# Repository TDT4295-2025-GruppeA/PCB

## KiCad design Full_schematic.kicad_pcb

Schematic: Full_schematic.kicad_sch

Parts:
C1: 1210, 2.2µF/100V; C_1210_3225Metric
C2, C3, C60, C62, C63, C64: 22u; C_0805_2012Metric
C4, C7, C8, C9, C11, C14, C16, C19, C20, C21, C22, C23, C24, C25, C28, C29, C30, C31, C32, C39, C44, C59, C61, C65, C66, C67, C68, C69, C70: 470n; C_0805_2012Metric
C5, C13, C15, C17, C50, C54, C57, C78, C83, C84, C85, C86, C87, C88, C90, C95, C96: 100n; C_0805_2012Metric
C6: 100u; C_0805_2012Metric
C10, C12, C56, C91, C99: 10u; C_0805_2012Metric
C26: 3.3n; C_0805_2012Metric
C33, C36, C37, C71, C72: 47u; C_0805_2012Metric
C34: 330u; CP_EIA-3216-10_Kemet-I
C35: 100u; CP_EIA-2012-15_AVX-P
C38, C40, C41, C42, C43, C45, C46, C47, C51, C52, C53, C55, C58, C73, C74, C75, C76, C77: 4.7u; C_0805_2012Metric
C48, C49, C89, C94: 1u; C_0805_2012Metric
C80, C82: 6pF; C_0805_2012Metric
C92, C93: 2.2u; C_0805_2012Metric
C97: 0.1uF; C_0805_2012Metric
C101, C102, C103: 1u; CP_EIA-2012-15_AVX-P
D1: IR26-21C_L110_TR8; LED_1206_3216Metric
IC1: XC7A100T-1FTG256C; FTG256_AMD; Manufacturer_Part_Number XC7A100T-1FTG256C
J1: FFC3B11-40-T; FH12A40S05SH55; PARTREV A; DigiKey_Part_Number 2073-FFC3B11-40-TCT-ND
J2: CONN14_877591414_MOL
J3: Conn_ST_STDC14; PinHeader_2x07_P1.27mm_Vertical_SMD
J4: AMPHENOL_10067847-001RLF
J5: USB_B_Micro; CONN_10118192-0002LF_AMP
JP1, JP2, JP3, JP4: G800W306018EU; AMPHENOL_G800W306018EU; PARTREV B
L1: 18uH; L_0805_2012Metric
L2, L3: 1.5u; L_0805_2012Metric
L4, L6: 2.2u; L_0805_2012Metric
R1: 30.1k; R_0805_2012Metric
R2, R4, R10: 22.1k; R_0805_2012Metric
R3: 6.81k; R_0805_2012Metric
R5: 200; R_0805_2012Metric
R6, R25, R26, R30, R33, R34: 100; R_0805_2012Metric
R7, R8: 100k; R_0805_2012Metric
R9: 73.2k; R_0805_2012Metric
R12, R13: 4.7k; R_0805_2012Metric
R14, R16, R18, R20, R21, R24, R29, R32, R35, R37, R39, R41: 536; R_0805_2012Metric
R15, R17, R19, R22, R27, R31, R36, R38, R40: 270; R_0805_2012Metric
R23, R28, R55: 10k; R_0805_2012Metric
R42: THB001P; XDCR_COM-09032
R45, R85, R86: 1k; R_0805_2012Metric
R46, R47, R48, R49, R50, R51, R52, R53, R54, R56, R57, R58, R59, R60, R61, R62, R63, R64, R65, R66, R67, R68, R69, R70, R71, R72, R73, R74: 220; R_0805_2012Metric
R75, R76, R77, R78: 47; R_0805_2012Metric
R79, R80, R81, R82, R83, R84: 10K; R_0805_2012Metric
U1: 2S7A_0518S1U; SIP4_2S7A_GAP
U2, U6: IS66WVE4M16EBLL-70BLI; SOP80P1184X119-44N; Manufacturer_Part_Number CY62157EV30LL-55ZSXE
U3: TPS54294PWP; PWP16_2P31X2P46
U4: TPS54325PWPR; PWP14_2P31X2P46
U5, U8: SN74ALVC245PWR; PW20
U7: S25FL127S; SOIC127P800X216-8N
U9, U11, U14, U16: MAN72A
U10, U12, U15, U17: MC14511BDG; SOIC-16_ONS
U13: STM32U545VETxQ; LQFP-100_14x14mm_P0.5mm
U18, U19: PTS645SM43SMTR92LFS; SWITCH_43SMTR92LFS
Y1: 100Hz; CB3LV3C100M000000
Y2: 48MHz; Crystal_SMD_2520-4Pin_2.5x2.0mm

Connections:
+1V0: C7.1, C9.1, C14.1, C19.1, C21.1, C23.1, C28.1, C31.1, C34.1, C35.1, C39.1, C40.1, C43.1, C44.1, C47.1, C52.1, C55.1, C58.1, C60.1, C63.1, IC1.E10 (VCCBRAM_1), IC1.F7 (VCCINT_1), IC1.F9 (VCCINT_2), IC1.F11 (VCCBRAM_2), IC1.G6 (VCCINT_3), IC1.H9 (VCCINT_4), IC1.J6 (VCCINT_5), IC1.K9 (VCCINT_6), IC1.L8 (VCCINT_7), JP3.1, JP3.2, L3.2, R3.1, U4.1 (VO)
+1V8: C2.1, C3.2, C24.1, C29.1, C32.1, C36.1, C41.1, C45.1, IC1.G8 (VCCADC_0), IC1.G10 (VCCAUX_1), IC1.J10 (VCCAUX_2), IC1.K11 (VCCAUX_3), IC1.L10 (VCCAUX_4), JP1.1, JP1.2, L2.1, R1.1
A2: IC1.A2 (IO_L8N_T1_AD14N_35), U2.44 (A5)
B1: IC1.B1 (IO_L9N_T1_DQS_AD7N_35), U2.43 (A6)
B2: IC1.B2 (IO_L8P_T1_AD14P_35), U2.42 (A7)
B4: IC1.B4 (IO_L4P_T0_35), U2.41 (~OE)
B5: IC1.B5 (IO_L2N_T0_AD12N_35), U2.40 (~BHE)
BLUE: R14.2, R15.2; also elsewhere on the board
BLUE0: IC1.T9 (IO_L22P_T3_A05_D21_14), U5.6 (A5)
BLUE1: IC1.T8 (IO_L21N_T3_DQS_A06_D22_14), U5.7 (A6)
BLUE2: IC1.T7 (IO_L21P_T3_DQS_14), U5.8 (A7)
BLUE3: IC1.T5 (IO_L23N_T3_A02_D18_14), U5.9 (A8)
C1: IC1.C1 (IO_L9P_T1_DQS_AD7P_35), U2.37 (I/O14)
C2: IC1.C2 (IO_L7N_T1_AD6N_35), U2.36 (I/O13)
C3: IC1.C3 (IO_L7P_T1_AD6P_35); also elsewhere on the board
C4: IC1.C4 (IO_L12N_T1_MRCC_35); also elsewhere on the board
C6: IC1.C6 (IO_L5N_T0_AD13N_35); also elsewhere on the board
C7: IC1.C7 (IO_L5P_T0_AD13P_35); also elsewhere on the board
D1: IC1.D1 (IO_L10N_T1_AD15N_35), U2.35 (I/O12)
D3: IC1.D3 (IO_L11N_T1_SRCC_35), U2.32 (I/O11)
D4: IC1.D4 (IO_L12P_T1_MRCC_35), U2.31 (I/O10)
D5: IC1.D5 (IO_L6N_T0_VREF_35); also elsewhere on the board
D6: IC1.D6 (IO_L6P_T0_35), U2.30 (I/O9)
D8: IC1.D8 (IO_L6P_T0_15); also elsewhere on the board
D16: IC1.D16 (IO_L17N_T2_A25_15), U13.1 (PE2)
E1: IC1.E1 (IO_L15N_T2_DQS_35), U2.29 (I/O8)
E2: IC1.E2 (IO_L10P_T1_AD15P_35), U2.28 (A8)
E3: IC1.E3 (IO_L11P_T1_SRCC_35), U2.27 (A9)
E5: IC1.E5 (IO_L13N_T2_MRCC_35), U2.26 (A10)
E6: IC1.E6 (IO_0_35), U2.25 (A11)
E8: IC1.E8 (CCLK_0), U7.6 (CLK)
F2: IC1.F2 (IO_L15P_T2_DQS_35), U2.24 (A12)
F3: IC1.F3 (IO_L14N_T2_SRCC_35), U2.23 (A13)
F4: IC1.F4 (IO_L14P_T2_SRCC_35), U2.22 (A14)
F5: IC1.F5 (IO_L13P_T2_MRCC_35), U2.21 (A15)
FPGA_DONE: IC1.H10 (DONE_0), R5.2, R6.2, U13.25 (PA3)
G1: IC1.G1 (IO_L17N_T2_35), U2.20 (A16)
G2: IC1.G2 (IO_L17P_T2_35), U2.19 (A17)
G4: IC1.G4 (IO_L16N_T2_35), U2.18 (A18)
G5: IC1.G5 (IO_L16P_T2_35), U2.17 (~WE)
G16: IC1.G16 (IO_L22N_T3_A16_15), U13.8 (PC14)
GREEN: R35.2, R36.2; also elsewhere on the board
GREEN0: IC1.T4 (IO_L9P_T1_DQS_34), U8.2 (A1)
GREEN1: IC1.T3 (IO_L9N_T1_DQS_34), U8.3 (A2)
GREEN2: IC1.T2 (IO_L8N_T1_34), U8.4 (A3)
GREEN3: IC1.R16 (IO_L9N_T1_DQS_D13_14), U8.5 (A4)
H1: IC1.H1 (IO_L20N_T3_35), U2.16 (I/O7)
H2: IC1.H2 (IO_L20P_T3_35), U2.15 (I/O6)
H3: IC1.H3 (IO_L21N_T3_DQS_35), U2.14 (I/O5)
H4: IC1.H4 (IO_L18N_T2_35), U2.13 (I/O4)
H5: IC1.H5 (IO_L18P_T2_35), U2.10 (I/O3)
HSYNC2: IC1.A7 (IO_L1N_T0_AD4N_35), J1.32
J1: IC1.J1 (IO_L22N_T3_35), U2.9 (I/O2)
J3: IC1.J3 (IO_L21P_T3_DQS_35), U2.8 (I/O1)
J5: IC1.J5 (IO_L19P_T3_35), U2.7 (I/O0)
J13: R25.2, U7.5 (SI/IO0)
J14: R26.1, U7.2 (SO/IO1)
J15: IC1.J15 (IO_L23P_T3_FOE_B_15), U13.15 (PC0)
J16: IC1.J16 (IO_L23N_T3_FWE_B_15), U13.16 (PC1)
K1: IC1.K1 (IO_L22P_T3_35), U2.6 (~CE)
K2: IC1.K2 (IO_L24N_T3_35), U2.5 (A0)
K3: IC1.K3 (IO_L24P_T3_35), U2.4 (A1)
K5: IC1.K5 (IO_25_35), U2.3 (A2)
K10: IC1.K10 (INIT_B_0), R12.1
K12: IC1.K12 (IO_0_14)
K13: IC1.K13 (IO_L5P_T0_D06_14)
K15: IC1.K15 (IO_L2P_T0_D02_14), U7.3 (WP#/IO2)
K16: R30.1, U7.7 (HOLD#/IO3/R#)
L2: IC1.L2 (IO_L23N_T3_35), U2.1 (A4)
L3: IC1.L3 (IO_L23P_T3_35), U2.2 (A3)
L9: IC1.L9 (PROGRAM_B_0), R13.1
L12: IC1.L12 (IO_L6P_T0_FCS_B_14)
L13: IC1.L13 (IO_L5N_T0_D07_14)
L14: IC1.L14 (IO_L4P_T0_D04_14), U6.22 (A14)
L15: IC1.L15 (IO_L3P_T0_DQS_PUDC_B_14), U6.21 (A15)
M4: IC1.M4 (IO_L1N_T0_34), U6.20 (A16)
M5: IC1.M5 (IO_L6P_T0_34), U6.19 (A17)
M6: IC1.M6 (IO_L19P_T3_A10_D26_14), U6.18 (A18)
M14: IC1.M14 (IO_L4N_T0_D05_14), U6.17 (~WE)
M15: IC1.M15 (IO_L3N_T0_DQS_EMCCLK_14), U6.16 (I/O7)
M16: IC1.M16 (IO_L7P_T1_D09_14), U6.15 (I/O6)
MCU_CS: IC1.H12 (IO_L20P_T3_A20_15), U13.31 (PA7)
MCU_MISO: IC1.H16 (IO_L22P_T3_A17_15), U13.23 (PA1)
MCU_MOSI: IC1.H14 (IO_L24P_T3_RS1_15), U13.24 (PA2)
MCU_SCK: IC1.H13 (IO_L20N_T3_A19_15), U13.30 (PA6)
MISO: J4.7 (DATA0), R80.2, U13.79 (PC11)
N1: IC1.N1 (IO_L4P_T0_34), U6.14 (I/O5)
N2: IC1.N2 (IO_L3N_T0_DQS_34), U6.13 (I/O4)
N3: IC1.N3 (IO_L3P_T0_DQS_34), U6.10 (I/O3)
N9: IC1.N9 (IO_L18P_T2_A12_D28_14), U6.9 (I/O2)
N11: IC1.N11 (IO_L13P_T2_MRCC_14), U6.8 (I/O1)
N12: IC1.N12 (IO_L13N_T2_MRCC_14), U6.7 (I/O0)
N13: IC1.N13 (IO_L11P_T1_SRCC_14), U6.6 (~CE)
N14: IC1.N14 (IO_L12P_T1_MRCC_14), U6.5 (A0)
N16: IC1.N16 (IO_L7N_T1_D10_14), U6.4 (A1)
unnamed: C92.1, C93.1, L6.2, U13.49 (VDD11), U13.98 (VDD11)
unnamed: D1.2 (A), R6.1
unnamed: IC1.C9 (IO_L1N_T0_AD0N_15), J1.11
unnamed: IC1.J14 (IO_L1N_T0_D01_DIN_14), R26.2
unnamed: IC1.C8 (IO_L1P_T0_AD0P_15), J1.12
unnamed: IC1.B7 (IO_L1P_T0_AD4P_35), U2.38 (I/O15)
unnamed: IC1.J13 (IO_L1P_T0_D00_MOSI_14), R25.1
unnamed: IC1.A9 (IO_L2N_T0_AD8N_15), J1.31
unnamed: IC1.K16 (IO_L2N_T0_D03_14), R30.2
unnamed: IC1.A8 (IO_L2P_T0_AD8P_15), J1.34
unnamed: IC1.B6 (IO_L2P_T0_AD12P_35), U2.39 (~BLE)
unnamed: IC1.A10 (IO_L3N_T0_DQS_AD1N_15), J1.30
unnamed: IC1.B9 (IO_L3P_T0_DQS_AD1P_15), J1.24
unnamed: IC1.B11 (IO_L4N_T0_15), J1.19
unnamed: IC1.B10 (IO_L4P_T0_15), J1.20
unnamed: IC1.A12 (IO_L5N_T0_AD9N_15), J1.28
unnamed: IC1.B12 (IO_L5P_T0_AD9P_15), J1.18
unnamed: IC1.A14 (IO_L7N_T1_AD2N_15), J1.26
unnamed: IC1.A13 (IO_L7P_T1_AD2P_15), J1.27
unnamed: IC1.B14 (IO_L8N_T1_AD10N_15), J1.17
unnamed: IC1.A15 (IO_L9N_T1_DQS_AD3N_15), J1.25
unnamed: IC1.B15 (IO_L9P_T1_DQS_AD3P_15), J1.16
unnamed: IC1.B16 (IO_L10N_T1_AD11N_15), J1.15
unnamed: IC1.C12 (IO_L11N_T1_SRCC_15), J1.9
unnamed: IC1.C11 (IO_L11P_T1_SRCC_15), J1.10
unnamed: IC1.C13 (IO_L12N_T1_MRCC_15), J1.8
unnamed: IC1.E11 (IO_L14P_T2_SRCC_15), Y1.3 (OUT)
unnamed: IC1.L7 (TCK_0), J2.6, R28.1
unnamed: IC1.N7 (TDI_0), J2.10
unnamed: IC1.N8 (TDO_0), J2.8
unnamed: IC1.M7 (TMS_0), J2.4, R23.1
unnamed: J3.6 (JCLK/SWCLK), R75.2
unnamed: J3.10 (JTDI/NC), R78.2
unnamed: J3.8 (JTDO/SWO), R77.2
unnamed: J3.4 (JTMS/SWDIO), R76.2
unnamed: J3.12 (~RST), U13.14 (NRST)
unnamed: J4.8 (DATA1), R79.2
unnamed: R15.1, R16.2, R17.2
unnamed: R17.1, R18.2, R19.2
unnamed: R19.1, R20.2
unnamed: R22.1, R24.2, R27.2
unnamed: R27.1, R29.2, R31.2
unnamed: R31.1, R32.2
unnamed: R36.1, R37.2, R38.2
unnamed: R38.1, R39.2, R40.2
unnamed: R40.1, R41.2
unnamed: L1.2, U1.1 (+VIN)
unnamed: J1.2, U1.6 (+VOUT)
unnamed: R7.1, U3.5 (EN1), U4.6 (PG)
unnamed: R8.2, U3.6 (PG1), U3.12 (EN2)
unnamed: C17.2, L2.2, U3.3 (SW1)
unnamed: C50.2, L4.1, U3.14 (SW2)
unnamed: C17.1, U3.2 (VBST1)
unnamed: C50.1, U3.15 (VBST2)
unnamed: R1.2, R2.1, U3.7 (VFB1)
unnamed: R9.2, R10.1, U3.10 (VFB2)
unnamed: C48.1, R8.1, U3.9 (VREG5)
unnamed: C26.1, U4.4 (SS)
unnamed: C54.2, L3.1, U4.10 (SW1), U4.11 (SW2)
unnamed: C54.1, U4.12 (VBST)
unnamed: R3.2, R4.1, U4.2 (VFB)
unnamed: C49.1, R7.2, U4.3 (VREG5)
unnamed: R32.1, U5.18 (B1)
unnamed: R29.1, U5.17 (B2)
unnamed: R24.1, U5.16 (B3)
unnamed: R21.1, U5.15 (B4)
unnamed: R20.1, U5.14 (B5)
unnamed: R18.1, U5.13 (B6)
unnamed: R16.1, U5.12 (B7)
unnamed: R14.1, U5.11 (B8)
unnamed: C78.1, U7.8 (VCC)
unnamed: C78.2, U7.4 (VSS)
unnamed: R41.1, U8.18 (B1)
unnamed: R39.1, U8.17 (B2)
unnamed: R37.1, U8.16 (B3)
unnamed: R35.1, U8.15 (B4)
unnamed: R34.1, U8.14 (B5)
unnamed: R33.1, U8.13 (B6)
unnamed: R52.2, U9.1 (A)
unnamed: R51.2, U9.13 (B)
unnamed: R50.2, U9.10 (C)
unnamed: R49.2, U9.8 (D)
unnamed: R48.2, U9.7 (E)
unnamed: R47.2, U9.2 (F)
unnamed: R46.2, U9.11 (G)
unnamed: R52.1, U10.13 (a)
unnamed: R51.1, U10.12 (b)
unnamed: R50.1, U10.11 (c)
unnamed: R49.1, U10.10 (d)
unnamed: R48.1, U10.9 (e)
unnamed: R47.1, U10.15 (f)
unnamed: R46.1, U10.14 (g)
unnamed: R60.2, U11.1 (A)
unnamed: R59.2, U11.13 (B)
unnamed: R58.2, U11.10 (C)
unnamed: R57.2, U11.8 (D)
unnamed: R56.2, U11.7 (E)
unnamed: R54.2, U11.2 (F)
unnamed: R53.2, U11.11 (G)
unnamed: R60.1, U12.13 (a)
unnamed: R59.1, U12.12 (b)
unnamed: R58.1, U12.11 (c)
unnamed: R57.1, U12.10 (d)
unnamed: R56.1, U12.9 (e)
unnamed: R54.1, U12.15 (f)
unnamed: R53.1, U12.14 (g)
unnamed: R76.1, U13.72 (PA13)
unnamed: R75.1, U13.76 (PA14)
unnamed: R78.1, U13.77 (PA15)
unnamed: R77.1, U13.89 (PB3)
unnamed: C80.1, U13.12 (PH0), Y2.1
unnamed: C82.1, U13.13 (PH1), Y2.3
unnamed: R55.2, U13.94 (PH3)
unnamed: L6.1, U13.46 (VLXSMPS)
unnamed: C89.2, C90.2, U13.20 (VREF+)
unnamed: R67.2, U14.1 (A)
unnamed: R66.2, U14.13 (B)
unnamed: R65.2, U14.10 (C)
unnamed: R64.2, U14.8 (D)
unnamed: R63.2, U14.7 (E)
unnamed: R62.2, U14.2 (F)
unnamed: R61.2, U14.11 (G)
unnamed: R67.1, U15.13 (a)
unnamed: R66.1, U15.12 (b)
unnamed: R65.1, U15.11 (c)
unnamed: R64.1, U15.10 (d)
unnamed: R63.1, U15.9 (e)
unnamed: R62.1, U15.15 (f)
unnamed: R61.1, U15.14 (g)
unnamed: R74.2, U16.1 (A)
unnamed: R73.2, U16.13 (B)
unnamed: R72.2, U16.10 (C)
unnamed: R71.2, U16.8 (D)
unnamed: R70.2, U16.7 (E)
unnamed: R69.2, U16.2 (F)
unnamed: R68.2, U16.11 (G)
unnamed: R74.1, U17.13 (a)
unnamed: R73.1, U17.12 (b)
unnamed: R72.1, U17.11 (c)
unnamed: R71.1, U17.10 (d)
unnamed: R70.1, U17.9 (e)
unnamed: R69.1, U17.15 (f)
unnamed: R68.1, U17.14 (g)
P1: IC1.P1 (IO_L4N_T0_34), U6.3 (A2)
P3: IC1.P3 (IO_L5N_T0_34), U6.2 (A3)
P4: IC1.P4 (IO_L5P_T0_34), U6.1 (A4)
P5: IC1.P5 (IO_L10P_T1_34), U6.44 (A5)
P6: IC1.P6 (IO_25_14), U6.43 (A6)
P8: IC1.P8 (IO_L20P_T3_A08_D24_14), U6.42 (A7)
P9: IC1.P9 (IO_L18N_T2_A11_D27_14), U6.41 (~OE)
P10: IC1.P10 (IO_L14P_T2_SRCC_14), U6.40 (~BHE)
P11: IC1.P11 (IO_L14N_T2_SRCC_14), U6.39 (~BLE)
P13: IC1.P13 (IO_L11N_T1_SRCC_14), U6.38 (I/O15)
P14: IC1.P14 (IO_L12N_T1_MRCC_14), U6.37 (I/O14)
P15: IC1.P15 (IO_L8P_T1_D11_14), U6.36 (I/O13)
P16: IC1.P16 (IO_L8N_T1_D12_14), U6.35 (I/O12)
PA8: U13.67 (PA8), U17.2 (C)
PA9: U13.68 (PA9), U17.1 (B)
PB10: U13.44 (PB10); also elsewhere on the board
PB11: U13.45 (PB11); also elsewhere on the board
PB13: U10.7 (A), U13.52 (PB13)
PB14: U10.6 (D), U13.53 (PB14)
PB15: U10.2 (C), U13.54 (PB15)
PC2: R42.2, R42.V2, U13.17 (PC2)
PC3: R42.2', R42.H2, U13.18 (PC3)
PC6: U13.63 (PC6), U15.1 (B)
PC7: U13.64 (PC7), U17.7 (A)
PC8: U13.65 (PC8), U17.6 (D)
PD8: U10.1 (B), U13.55 (PD8)
PD9: U12.7 (A), U13.56 (PD9)
PD10: U12.6 (D), U13.57 (PD10)
PD11: U12.2 (C), U13.58 (PD11)
PD12: U12.1 (B), U13.59 (PD12)
PD13: U13.60 (PD13), U15.7 (A)
PD14: U13.61 (PD14), U15.6 (D)
PD15: U13.62 (PD15), U15.2 (C)
PE9: C101.1, R42.B, R42.B1A, R45.1, U13.37 (PE9)
PE10: C102.1, R85.1, U13.38 (PE10), U18.3
PE11: C103.1, R86.1, U13.39 (PE11), U19.3
PE12: U13.40 (PE12); also elsewhere on the board
PE13: U13.41 (PE13); also elsewhere on the board
PE14: U13.42 (PE14); also elsewhere on the board
PE15: U13.43 (PE15); also elsewhere on the board
R1: IC1.R1 (IO_L7N_T1_34), U6.32 (I/O11)
R2: IC1.R2 (IO_L7P_T1_34), U6.30 (I/O9)
R3: IC1.R3 (IO_L8P_T1_34), U6.31 (I/O10)
R5: IC1.R5 (IO_L23P_T3_A03_D19_14), U6.29 (I/O8)
R6: IC1.R6 (IO_L24P_T3_A01_D17_14), U6.28 (A8)
R7: IC1.R7 (IO_L24N_T3_A00_D16_14), U6.27 (A9)
R8: IC1.R8 (IO_L20N_T3_A07_D23_14), U6.26 (A10)
R10: IC1.R10 (IO_L17P_T2_A14_D30_14), U6.25 (A11)
R11: IC1.R11 (IO_L17N_T2_A13_D29_14), U6.24 (A12)
R12: IC1.R12 (IO_L15P_T2_DQS_RDWR_B_14), U6.23 (A13)
RED: R21.2, R22.2; also elsewhere on the board
RED0: IC1.T15 (IO_L10N_T1_D15_14), U5.2 (A1)
RED1: IC1.T14 (IO_L10P_T1_D14_14), U5.3 (A2)
RED2: IC1.T13 (IO_L16N_T2_A15_D31_14), U5.4 (A3)
RED3: IC1.T10 (IO_L22N_T3_A04_D20_14), U5.5 (A4)
SCK: J4.5 (CLK), U13.78 (PC10)
T12: IC1.T12 (IO_L15N_T2_DQS_DOUT_CSO_B_14), U7.1 (CS#)
VSYNC2: IC1.A5 (IO_L3P_T0_DQS_AD5P_35), J1.33

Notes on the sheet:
VCCINT
VGA_G3 VGA_G2 VGA_G1 VGA_G0
VGA_R3 VGA_R2 VGA_R1 VGA_R0
VCCBRAM
VCCO (14,15)
VCCAUX
VGA_VS VGA_HS
VGA_B3 VGA_B2 VGA_B1 VGA_B0
18V
S25FL128SAGMFI000
VCCO (34,35)

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
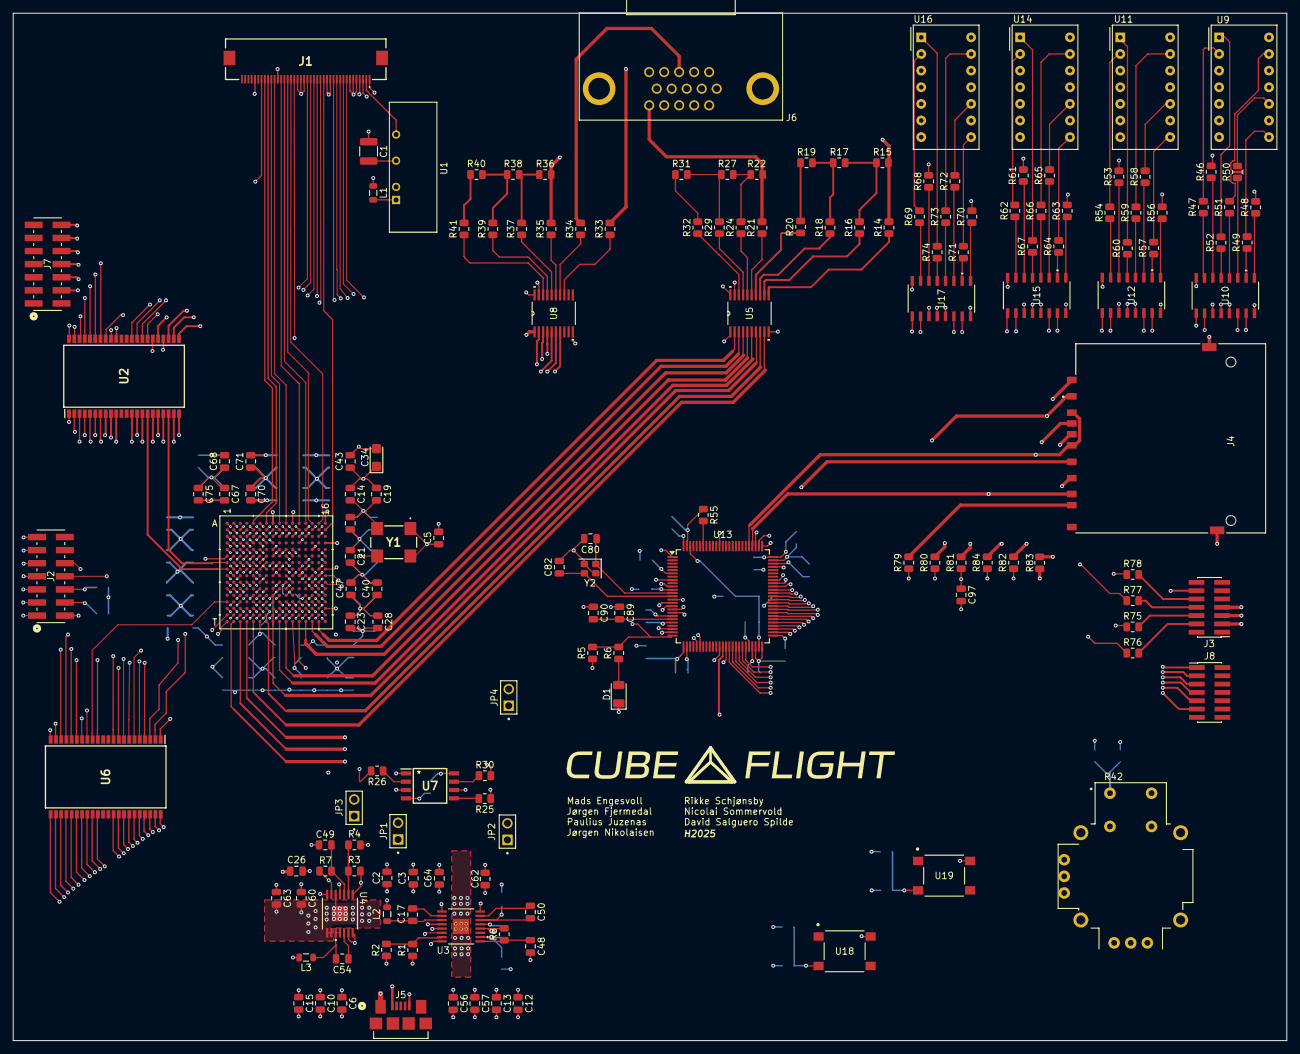
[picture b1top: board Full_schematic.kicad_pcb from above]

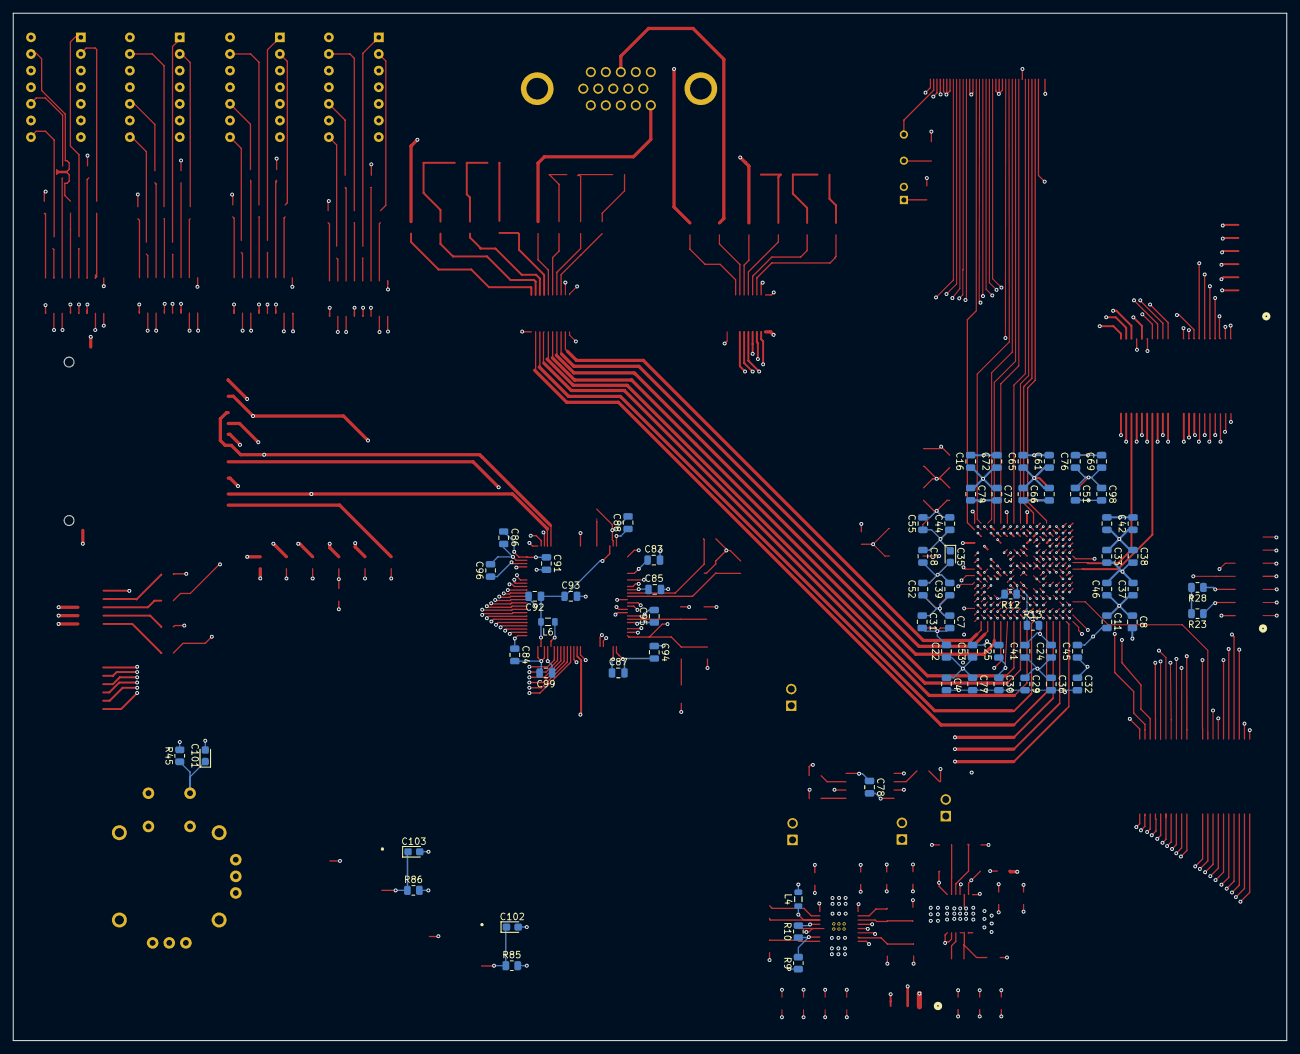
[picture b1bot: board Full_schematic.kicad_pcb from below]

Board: 8 copper layers, 194.5 x 156.9 mm, 221 parts (68 on the bottom side), 304 nets.

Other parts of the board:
C98: 100n; C_0805_2012Metric
J6: AHDF15A-KG-TAXB; CONN_AHDF15A-KG-TAXB_ASM
J7: CONN14_877591414_MOL
J8: Conn_ST_STDC14; PinHeader_2x07_P1.27mm_Vertical_SMD

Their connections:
BLUE: J6.3; also elsewhere on the board
C3: J7.4; also elsewhere on the board
C4: J7.6; also elsewhere on the board
C6: J7.10; also elsewhere on the board
C7: J7.12; also elsewhere on the board
D5: J7.8; also elsewhere on the board
D8: J7.14; also elsewhere on the board
GREEN: J6.2; also elsewhere on the board
PB10: J8.3; also elsewhere on the board
PB11: J8.1; also elsewhere on the board
PE12: J8.11; also elsewhere on the board
PE13: J8.9; also elsewhere on the board
PE14: J8.7; also elsewhere on the board
PE15: J8.5; also elsewhere on the board
RED: J6.1; also elsewhere on the board

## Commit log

2025-09-08 fpga power source schematic
2025-09-08 Added imported symbols folder
2025-09-08 Added imported footprints folder
2025-09-11 FPGA power source passes ERC
2025-09-11 Add: fpga .sch
2025-09-12 Basic FPGA schematic
2025-09-12 layout changes
2025-09-12 Added MCU symbol and footprint
2025-09-12 Added MCU file
2025-09-12 gitignore ds store
2025-09-12 lck ignore
2025-09-15 VGA design
2025-09-16 Add SD card module
2025-09-18 MCU SD-card merge
2025-09-18 link fpga to root
2025-09-18 link fpga
2025-09-18 alt i en
2025-09-18 ignore .zip
2025-09-19 schematic for stm32u545
2025-09-22 Added controllers
2025-09-22 full
2025-09-22 koble vga-fpga
2025-09-22 Added display connector
2025-09-22 Added power supply to LED backlight
2025-09-22 Added display power supply to full schematic
2025-09-23 fpga script
2025-09-23 update script
2025-09-23 Connected controllers and 7-segment display to mcu
2025-09-25 commit melding
2025-09-25 updated annotation
2025-09-25 C and R footprints
2025-09-26 updated footprints
2025-09-29 Fixed schematic comments
2025-09-29 --amend
2025-09-29 Connected FPGA DONE to MCU
2025-09-29 Added footprints for connectors and oscillators
2025-09-30 gitty comitty
2025-09-30 vga og dpi
2025-09-30 Placed mcu capacitors in pcb editor
2025-09-30 pbc edit: mcu debug connector + sd card
2025-09-30 vanskelig å merge lettere å copy paste
2025-09-30 pcb edit: buttons
2025-09-30 hippity gititty
2025-09-30 pcb edit: joystick
2025-10-01 Merged pcb edits in main
2025-10-01 wired mcu to peripherals
2025-10-02 davids arbeidsøkt
2025-10-03 Fixed some fpga routing and other small changes
2025-10-03 Made wires prettier
2025-10-03 Connected debug conn to fpga ++
2025-10-07 finished first draft of pcb
2025-10-09 gitty committy
2025-10-09 hook up hsync and vsync to screen (33 -> A5 and 32 -> A7)
2025-10-09 fix power under FPGA
2025-10-09 Fixed no connection on power ground for screen connector and 7 seg
2025-10-09 add half of jumpers
2025-10-09 gittyy comitty
2025-10-09 Heatsinks ++
2025-10-09 Added debug connector footprint++
2025-10-10 Added extra pin header footprints
2025-10-10 connected extra header to fpga, 4 extra connections between mcu and fpga and made pcb smaller
2025-10-10 Added logo
2025-10-10 Sized down
2025-10-10 Small fixes
2025-10-10 More small fixes
2025-10-10 Even more fixes
2025-10-10 Even even more fixes
2025-10-13 Fixed most of the DRC violations
2025-10-13 Fixed VGA conn holes
2025-10-13 Excluded violations
2025-10-13 updates to schematic
